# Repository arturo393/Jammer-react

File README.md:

# 🚨 Jammer-React

Sistema de complemento anti-jamming diseñado para dispositivos Teltonika FMA120, con arquitectura basada en FreeRTOS y comunicación Bluetooth.

## 📋 Descripción

El sistema Jammer-React es un dispositivo de seguridad vehicular que detecta y responde a intentos de jamming de señales GPS/GSM. Está diseñado para trabajar como complemento de los dispositivos Teltonika FMA120, proporcionando una capa adicional de protección contra interferencias maliciosas.

### 🎯 Características Principales

- **Detección automática de jamming** en tiempo real
- **Sistema de corta corriente** configurable 
- **Comunicación Bluetooth** para configuración remota
- **Sensor de puerta** integrado
- **Monitoreo de memoria** con comando de diagnóstico
- **LED indicador** de estados del sistema
- **Compatible con FreeRTOS**

## 🔧 Protocolo de Funcionamiento

### Algoritmo Principal

1. **Monitoreo Continuo**: Se revisa constantemente la entrada `JAMIN`
2. **Detección de Jamming**: Si `JAMIN == LOW`:
   - `JAMOUT = LOW` por 90 segundos
   - `DOUT` intercambia entre LOW y abierto durante 90 segundos
   - Se entra en **modo alarma** durante 90 segundos
3. **Activación por Puerta**: Si durante el modo alarma `DOORIN == Abierto`:
   - `JAMOUT = LOW` durante 5 minutos después que termine el modo alarma

### Estados del Sistema

- **Normal**: Monitoreo continuo sin detección de jamming
- **Alarma**: Jamming detectado, activación de contramedidas
- **Puerta Abierta**: Extensión del modo de protección

## 🏗️ Estructura del Proyecto

```
Jammer-react/
├── Hardware/              # Diseños de PCB y esquemáticos
│   ├── v1/               # Versión 1 del hardware
│   └── v2/               # Versión 2 del hardware
├── JammerRTOS/           # Código principal con FreeRTOS
├── jammerv2/             # Versión 2 del firmware
├── jammerv3/             # Versión 3 del firmware (sin FreeRTOS)
├── Simulation/           # Simulaciones SPICE
├── case/                 # Archivos para carcasa
├── logos/                # Recursos gráficos
├── CHANGELOG.md          # Historial de cambios
├── RELEASE_NOTES.md      # Notas de la versión actual
└── README.md            # Este archivo
```

## 🚀 Instalación y Configuración

### Prerrequisitos

- **PlatformIO** instalado
- **Arduino IDE** (opcional)
- Microcontrolador compatible con **ESP32/Arduino**
- Dispositivo **Teltonika FMA120**

### Configuración del Hardware

1. Conectar las entradas según el esquemático en `/Hardware/v2/`
2. Configurar los pines según la definición en el código
3. Verificar las conexiones de alimentación

### Compilación

```bash
# Usando PlatformIO
cd JammerRTOS
pio run

# Para upload
pio run --target upload
```

## 📊 Versiones

### Actual: v2.1 (Rama optimization)
- ✅ Función F() para mejora de estabilidad
- ✅ Comando `memtest` para diagnóstico
- ✅ Sistema de lectura de memoria mejorado
- 🔄 En pruebas: Optimizaciones del corta corriente

### Historial de Versiones

- **v2.1** (2018-12-18): Funciones Bluetooth y estado no volátil
- **v2.0** (2018-11-29): Reestructuración completa del código
- **v1.9.0** (2018-08-21): Correcciones críticas de estabilidad
- **v1.1** (2018-02-20): Variables de estado y sensores
- **v1.0** (2017-12-01): Versión inicial estable

Ver [CHANGELOG.md](CHANGELOG.md) para detalles completos.

## 🛠️ Configuración via Bluetooth

El sistema permite configuración remota via Bluetooth:

- **ID del dispositivo**: Configuración única por unidad
- **Estados del sistema**: Monitoreo en tiempo real
- **Parámetros de funcionamiento**: Ajuste de tiempos y umbrales
- **Comando memtest**: Diagnóstico de memoria

## 🔍 Diagnóstico y Debug

### Comando memtest
```
memtest
```
Proporciona información sobre:
- Uso actual de memoria
- Memoria disponible
- Estado de las tareas FreeRTOS

### LEDs Indicadores
- **LED Principal**: Estado general del sistema
- **Durante Alarma**: Parpadeo característico
- **Modo Configuración**: Patrón específico

## 📈 Especificaciones Técnicas

| Característica | Especificación |
|----------------|----------------|
| Microcontrolador | ESP32/Arduino compatible |
| Voltaje de operación | 12V DC |
| Consumo | <100mA en standby |
| Temperatura | -20°C a +60°C |
| Comunicación | Bluetooth 2.0/4.0 |
| Entradas digitales | 3 (JAMIN, DOORIN, GPS) |
| Salidas digitales | 2 (JAMOUT, DOUT) |

## 🤝 Contribución

1. Fork el proyecto
2. Crea una rama para tu feature (`git checkout -b feature/AmazingFeature`)
3. Commit tus cambios (`git commit -m 'Add some AmazingFeature'`)
4. Push a la rama (`git push origin feature/AmazingFeature`)
5. Abre un Pull Request

## 📝 Licencia

Este proyecto está bajo la licencia especificada en el archivo [LICENSE](LICENSE).

## 👨‍💻 Autor

**Arturo Veras** - [@arturo393](https://github.com/arturo393)

## 📞 Soporte

Para soporte técnico o preguntas:
- Abre un [issue](https://github.com/arturo393/Jammer-react/issues)
- Consulta la documentación en [RELEASE_NOTES.md](RELEASE_NOTES.md)

---

⚠️ **Nota**: Este sistema está diseñado para uso legítimo de seguridad vehicular. Asegúrate de cumplir con las regulaciones locales sobre dispositivos de radiofrecuencia.

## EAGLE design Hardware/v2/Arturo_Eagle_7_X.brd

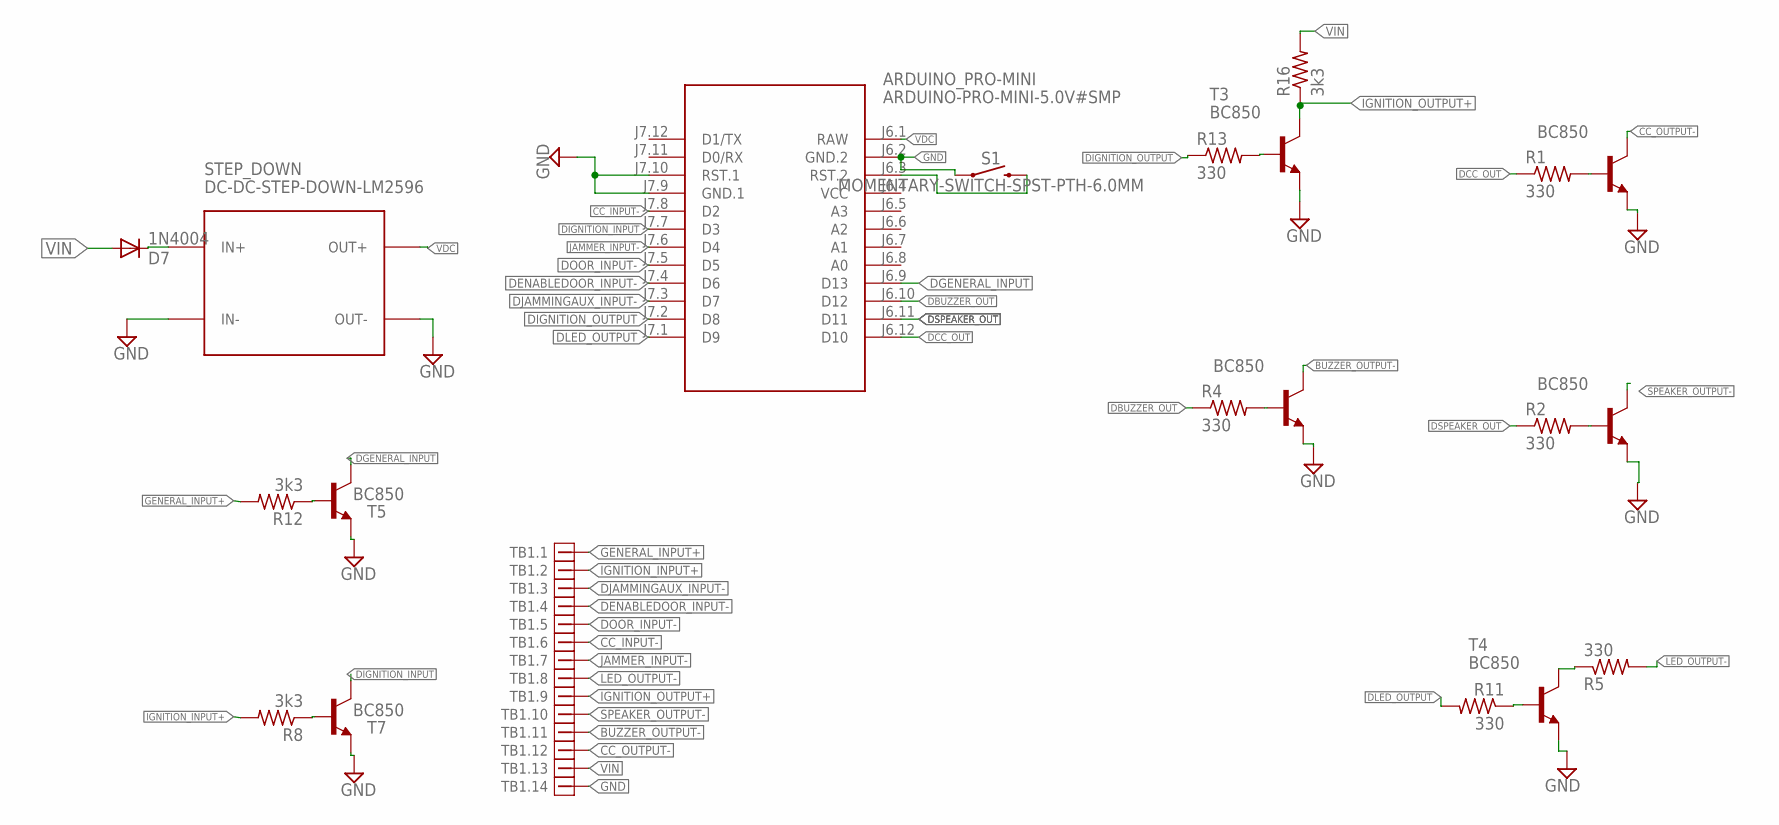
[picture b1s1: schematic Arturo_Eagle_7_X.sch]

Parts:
ARDUINO_PRO-MINI: ARDUINO-PRO-MINI-5.0V#SMP; ARDUINO-PRO-MINI#SMP
D7: 1N4004; DO41-10
R1, R2, R4, R5, R11, R13: 330; R0805
R8, R12, R16: 3k3; R0805
S1: MOMENTARY-SWITCH-SPST-PTH-6.0MM; TACTILE_SWITCH_PTH_6.0MM
STEP_DOWN: DC-DC-STEP-DOWN-LM2596
T1, T3, T4, T5, T6, T7, T8: BC850; SOT23
TB1: TB_PHOENIX; TERMINAL_BLOCK_14POS

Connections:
BUZZER_OUTPUT-: T6.3 (C), TB1.11, TB1.25
CC_INPUT-: ARDUINO_PRO-MINI.J7.8 (D2), TB1.6, TB1.20
CC_OUTPUT-: T8.3 (C), TB1.12, TB1.26
DBUZZER_OUT: ARDUINO_PRO-MINI.J6.10 (D12), R4.1
DCC_OUT: ARDUINO_PRO-MINI.J6.12 (D10), R1.1
DENABLEDOOR_INPUT-: ARDUINO_PRO-MINI.J7.4 (D6), TB1.4, TB1.18
DGENERAL_INPUT: ARDUINO_PRO-MINI.J6.9 (D13), T5.3 (C)
DIGNITION_INPUT: ARDUINO_PRO-MINI.J7.7 (D3), T7.3 (C)
DIGNITION_OUTPUT: ARDUINO_PRO-MINI.J7.2 (D8), R13.1
DJAMMINGAUX_INPUT-: ARDUINO_PRO-MINI.J7.3 (D7), TB1.3, TB1.17
DLED_OUTPUT: ARDUINO_PRO-MINI.J7.1 (D9), R11.2
DOOR_INPUT-: ARDUINO_PRO-MINI.J7.5 (D5), TB1.5, TB1.19
DSPEAKER_OUT: ARDUINO_PRO-MINI.J6.11 (D11), R2.1
GENERAL_INPUT+: R12.2, TB1.1, TB1.15
GND: ARDUINO_PRO-MINI.J6.2 (GND.2), ARDUINO_PRO-MINI.J7.9 (GND.1), ARDUINO_PRO-MINI.J7.10 (RST.1), S1.1, STEP_DOWN.IN-, STEP_DOWN.OUT-, T1.2 (E), T3.2 (E), T4.2 (E), T5.2 (E), T6.2 (E), T7.2 (E), T8.2 (E), TB1.14, TB1.28
IGNITION_INPUT+: R8.2, TB1.2, TB1.16
IGNITION_OUTPUT+: R16.1, T3.3 (C), TB1.9, TB1.23
JAMMER_INPUT-: ARDUINO_PRO-MINI.J7.6 (D4), TB1.7, TB1.21
LED_OUTPUT-: R5.2, TB1.8, TB1.22
unnamed: R12.1, T5.1 (B)
unnamed: R13.2, T3.1 (B)
unnamed: R1.2, T8.1 (B)
unnamed: R2.2, T1.1 (B)
unnamed: R4.2, T6.1 (B)
unnamed: R5.1, T4.3 (C)
unnamed: ARDUINO_PRO-MINI.J6.3 (RST.2), S1.3 (2)
unnamed: R11.1, T4.1 (B)
unnamed: R8.1, T7.1 (B)
unnamed: D7.C, STEP_DOWN.IN+
SPEAKER_OUTPUT-: T1.3 (C), TB1.10, TB1.24
VCC: ARDUINO_PRO-MINI.J6.4 (VCC)
VDC: ARDUINO_PRO-MINI.J6.1 (RAW), STEP_DOWN.OUT+
VIN: D7.A, R16.2, TB1.13, TB1.27

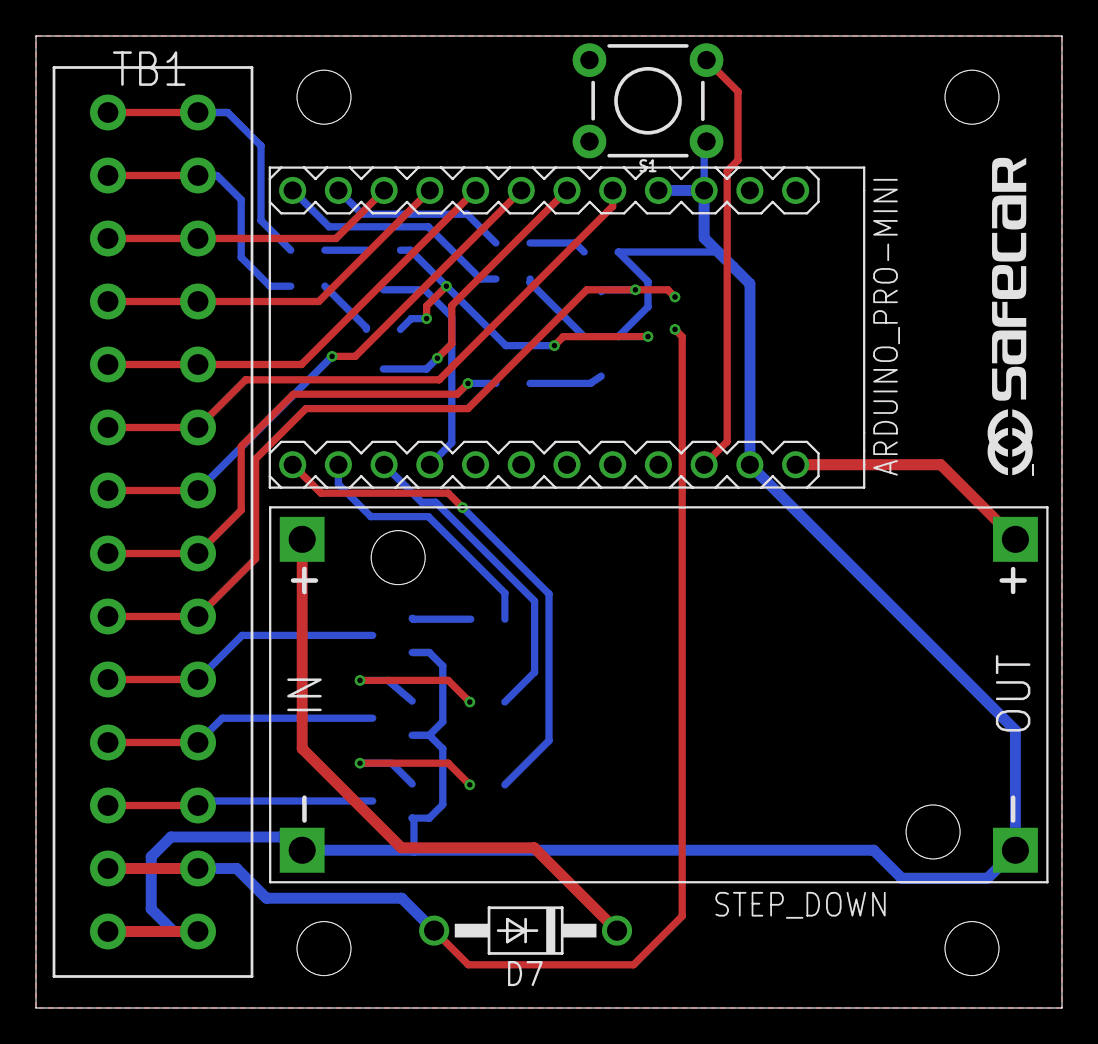
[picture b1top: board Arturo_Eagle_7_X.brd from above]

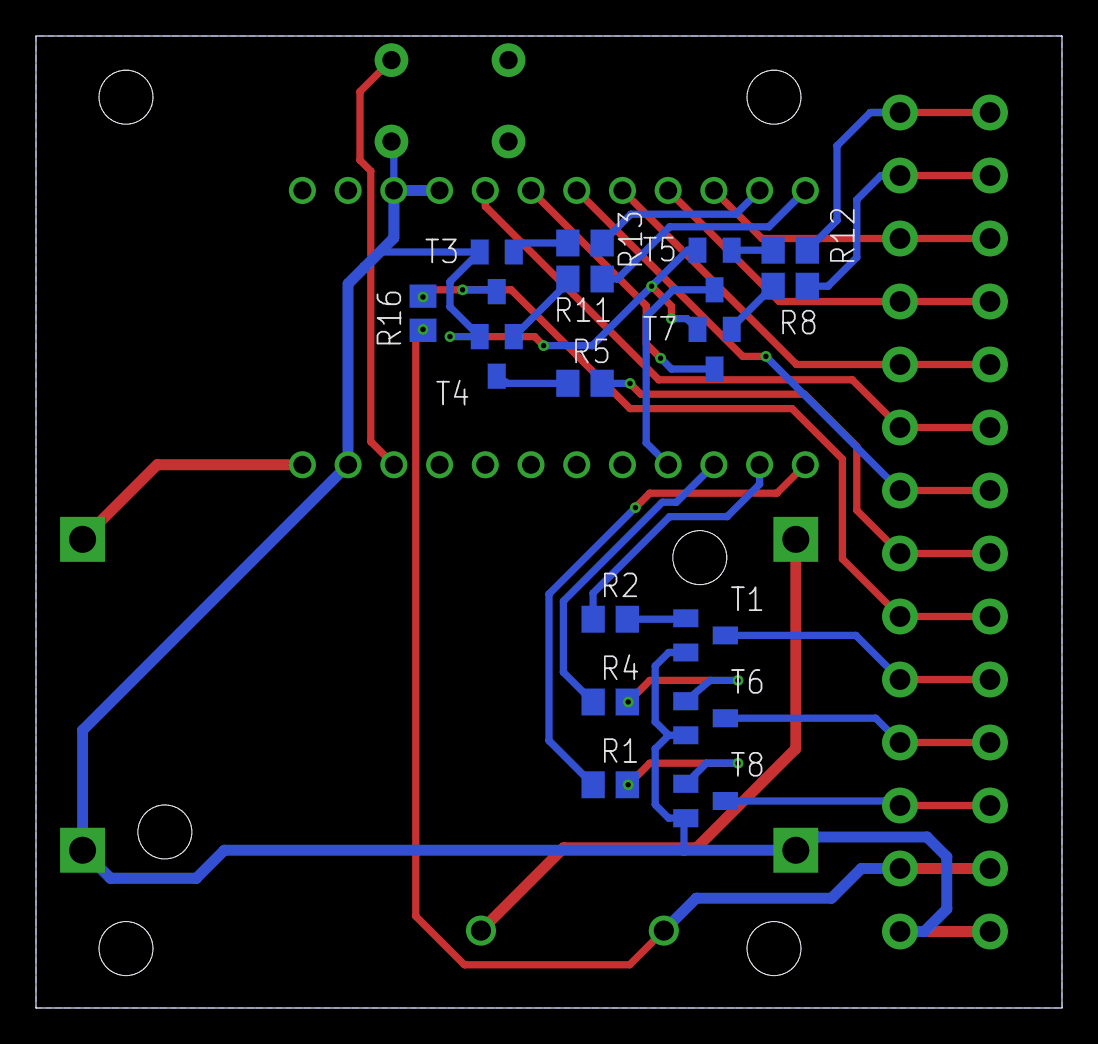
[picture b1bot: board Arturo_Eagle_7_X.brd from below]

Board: 2 copper layers, 57.0 x 54.0 mm, 21 parts (16 on the bottom side), 32 nets.

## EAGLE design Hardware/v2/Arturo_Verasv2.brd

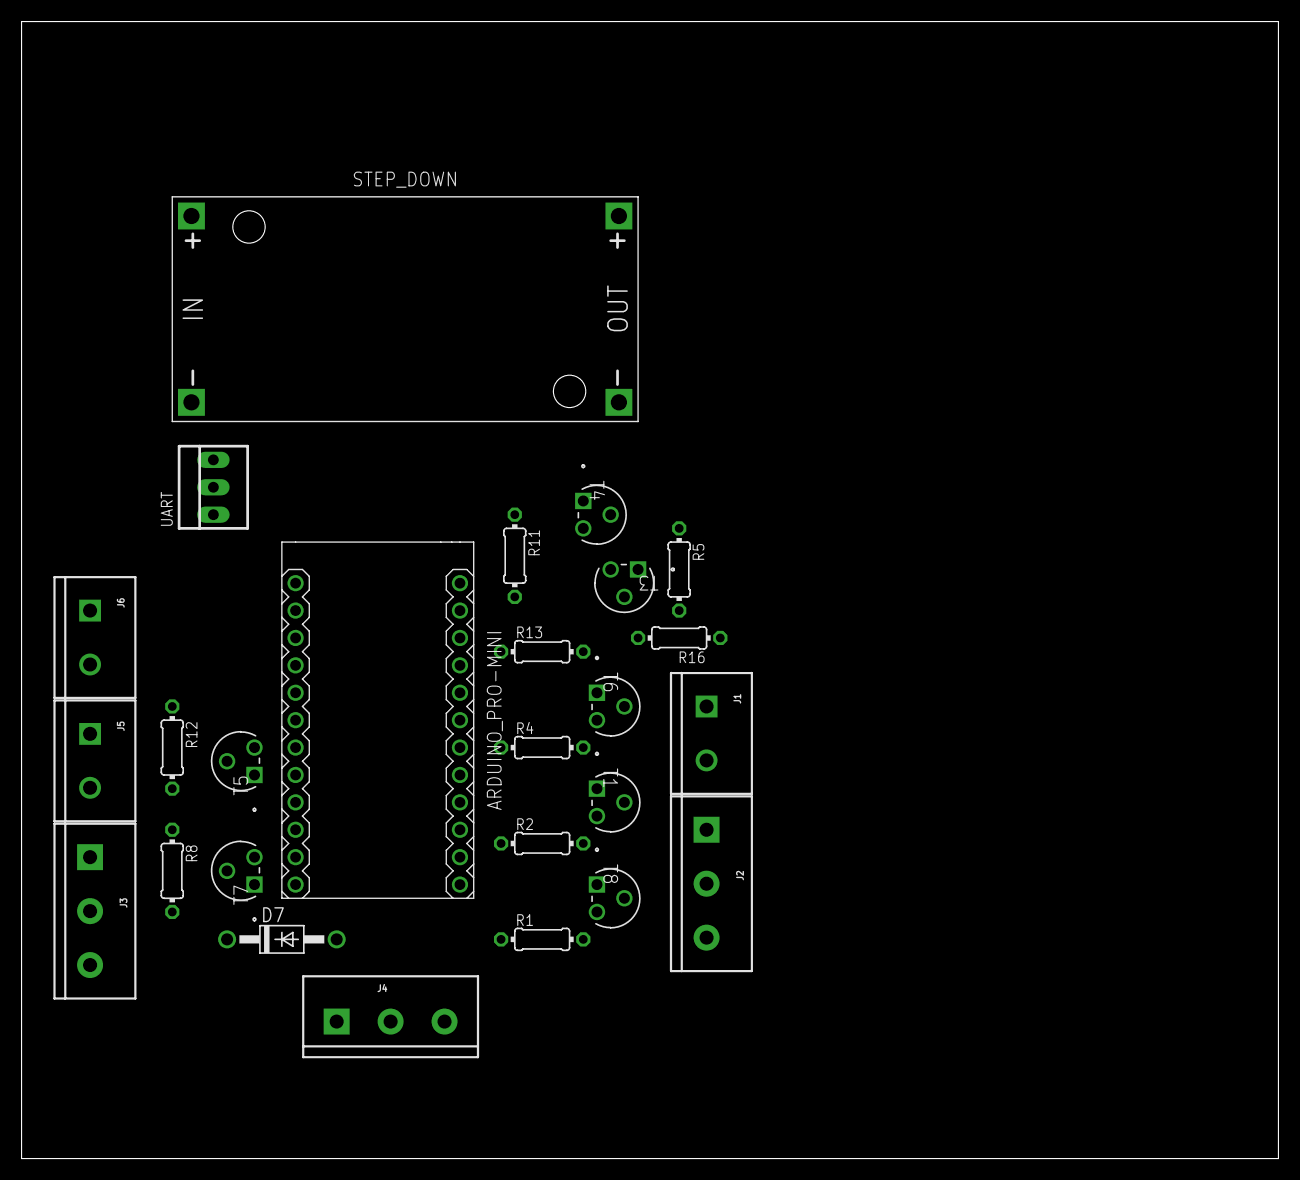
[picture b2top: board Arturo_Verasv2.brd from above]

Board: 2 copper layers, 116.5 x 105.4 mm, 26 parts (0 on the bottom side), 34 nets, no tracks yet.

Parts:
ARDUINO_PRO-MINI: ARDUINO-PRO-MINI-5.0V#SMP; ARDUINO-PRO-MINI#SMP
D7: 1N4004; DO41-10
J1, J5, J6: SCREWTERMINAL-5MM-2
J2, J3, J4: SCREWTERMINAL-5MM-3
R1, R2, R4, R5, R13: 330; 0204/7
R8, R12, R16: 3k3; 0204/7
R11: 47k; 0204/7
STEP_DOWN: DC-DC-STEP-DOWN-LM2596
T1, T3, T4, T5, T6, T7, T8: MPSA06; TO-92_2
UART: 22-23-2031

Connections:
BUZZER_OUTPUT-: J1.2, T6.3
CC_OUTPUT-: J2.2, T8.3
DBUZZER_OUT: ARDUINO_PRO-MINI.J6.10, R4.1
DCC_OUT: ARDUINO_PRO-MINI.J6.12, R1.1
DDOOR_INPUT-: ARDUINO_PRO-MINI.J7.1, J3.3
DENABLEDOOR_INPUT-: ARDUINO_PRO-MINI.J7.4, J3.1
DGENERAL_INPUT: ARDUINO_PRO-MINI.J7.5, T5.3
DIGNITION_INPUT: ARDUINO_PRO-MINI.J7.2, T7.3
DJAMMINGAUX_INPUT-: ARDUINO_PRO-MINI.J7.7, J6.2
DLED_OUTPUT: ARDUINO_PRO-MINI.J7.3, R11.2
DSPEAKER_OUT: ARDUINO_PRO-MINI.J6.11, R2.1
DTDIN2_OUT-: ARDUINO_PRO-MINI.J6.9, R13.1
DTDOUT1_INPUT-: ARDUINO_PRO-MINI.J7.6, J5.1
DTDOUT2_INPUT-: ARDUINO_PRO-MINI.J7.8, J6.1
GENERAL_INPUT+: J5.2, R12.2
GND: ARDUINO_PRO-MINI.J6.2, J4.2, R16.1, STEP_DOWN.IN-, STEP_DOWN.OUT-, T1.1, T4.1, T5.1, T6.1, T7.1, T8.1
IGNITION_INPUT+: J3.2, R8.2
LED_OUTPUT-: J2.3, R5.2
unnamed: R12.1, T5.2
unnamed: R13.2, T3.2
unnamed: R1.2, T8.2
unnamed: R2.2, T1.2
unnamed: R4.2, T6.2
unnamed: R5.1, T4.3
unnamed: ARDUINO_PRO-MINI.J7.12, UART.3
unnamed: ARDUINO_PRO-MINI.J7.11, UART.2
unnamed: ARDUINO_PRO-MINI.J7.9, UART.1
unnamed: R11.1, T4.2
unnamed: R8.1, T7.2
unnamed: D7.C, STEP_DOWN.IN+
SPEAKER_OUTPUT-: J2.1, T1.3
TDIN2_OUTPUT+: J1.1, R16.2, T3.1
VIN: D7.A, J4.1, T3.3
VOUT: ARDUINO_PRO-MINI.J6.1, J4.3, STEP_DOWN.OUT+

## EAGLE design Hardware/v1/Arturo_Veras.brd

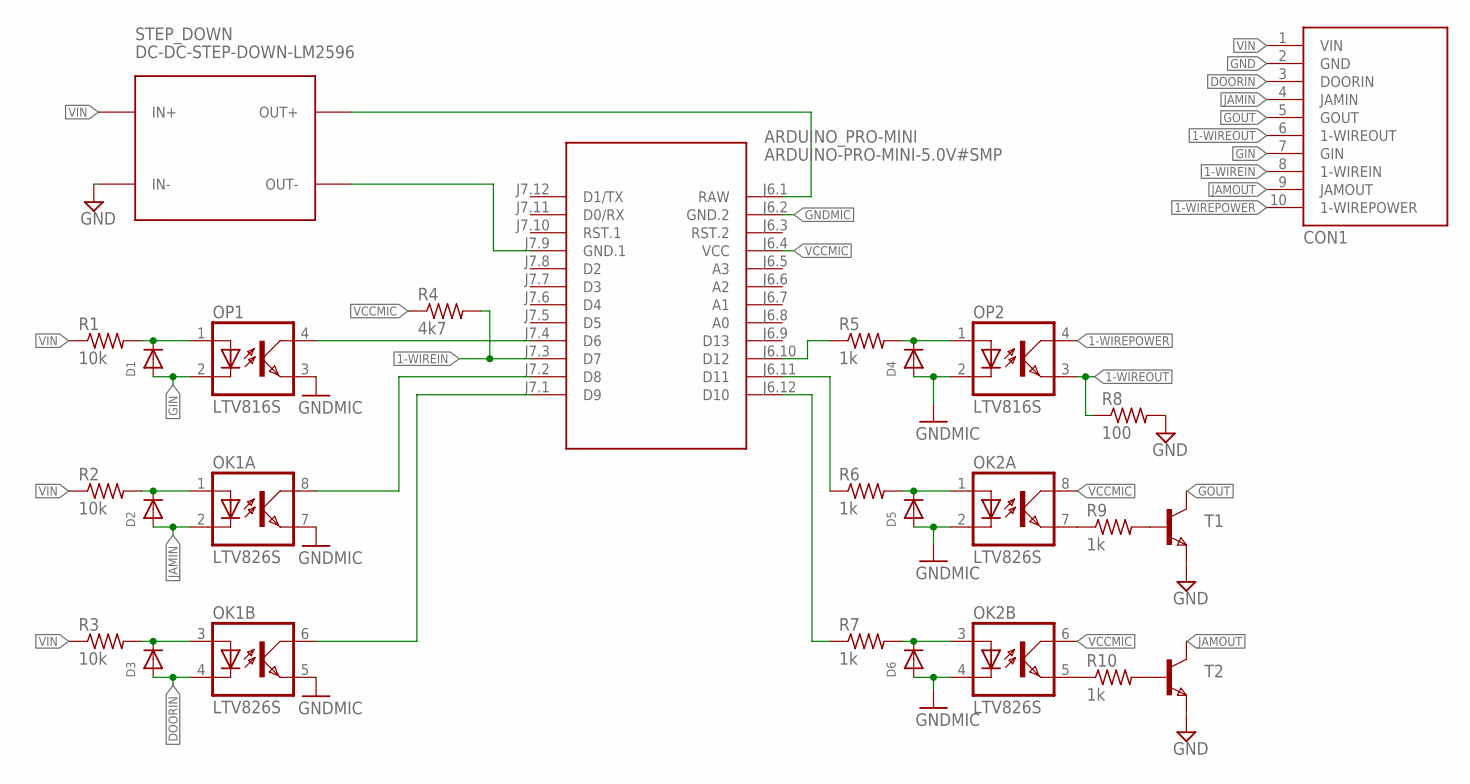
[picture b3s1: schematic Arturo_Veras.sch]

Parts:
ARDUINO_PRO-MINI: ARDUINO-PRO-MINI-5.0V#SMP; ARDUINO-PRO-MINI#SMP
CON1: TIN_HEADER_10POS; MICRO_MATE_N_LOK_TRUEHOLE_10POS
D1, D2, D3, D4, D5, D6: DIODESOD-323F; SOD-323F
OK1, OK2: LTV826S; DIL8-SMD
OP1, OP2: LTV816S; SMD4
R1, R2, R3: 10k; R0603
R4: 4k7; R0603
R5, R6, R7, R9, R10: 1k; R0603
R8: 100; R0603
STEP_DOWN: DC-DC-STEP-DOWN-LM2596
T1, T2: PBSS4360Z; SOT223

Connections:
1-WIREIN: ARDUINO_PRO-MINI.J7.3 (D7), CON1.8 (1-WIREIN), R4.2
1-WIREOUT: CON1.6 (1-WIREOUT), OP2.3 (EMIT), R8.1
1-WIREPOWER: CON1.10 (1-WIREPOWER), OP2.4 (COL)
DOORIN: CON1.3 (DOORIN), D3.A, OK1.4 (C)
GIN: CON1.7 (GIN), D1.A, OP1.2 (C)
GND: CON1.2 (GND), R8.2, STEP_DOWN.IN-, T1.3 (E), T2.3 (E)
GNDMIC: ARDUINO_PRO-MINI.J6.2 (GND.2), D4.A, D5.A, D6.A, OK1.5 (EMIT), OK1.7 (EMIT), OK2.2 (C), OK2.4 (C), OP1.3 (EMIT), OP2.2 (C)
GOUT: CON1.5 (GOUT), T1.2 (C), T1.4 (C)
JAMIN: CON1.4 (JAMIN), D2.A, OK1.2 (C)
JAMOUT: CON1.9 (JAMOUT), T2.2 (C), T2.4 (C)
unnamed: ARDUINO_PRO-MINI.J7.9 (GND.1), STEP_DOWN.OUT-
unnamed: ARDUINO_PRO-MINI.J6.1 (RAW), STEP_DOWN.OUT+
unnamed: ARDUINO_PRO-MINI.J7.4 (D6), OP1.4 (COL)
unnamed: D1.C, OP1.1 (A), R1.2
unnamed: ARDUINO_PRO-MINI.J6.10 (D12), R5.1
unnamed: D2.C, OK1.1 (A), R2.2
unnamed: ARDUINO_PRO-MINI.J7.2 (D8), OK1.8 (COL)
unnamed: D3.C, OK1.3 (A), R3.2
unnamed: D4.C, OP2.1 (A), R5.2
unnamed: ARDUINO_PRO-MINI.J7.1 (D9), OK1.6 (COL)
unnamed: OK2.7 (EMIT), R9.1
unnamed: ARDUINO_PRO-MINI.J6.11 (D11), R6.1
unnamed: D5.C, OK2.1 (A), R6.2
unnamed: ARDUINO_PRO-MINI.J6.12 (D10), R7.1
unnamed: D6.C, OK2.3 (A), R7.2
unnamed: OK2.5 (EMIT), R10.1
unnamed: R9.2, T1.1 (B)
unnamed: R10.2, T2.1 (B)
VCCMIC: ARDUINO_PRO-MINI.J6.4 (VCC), OK2.6 (COL), OK2.8 (COL), R4.1
VIN: CON1.1 (VIN), R1.1, R2.1, R3.1, STEP_DOWN.IN+

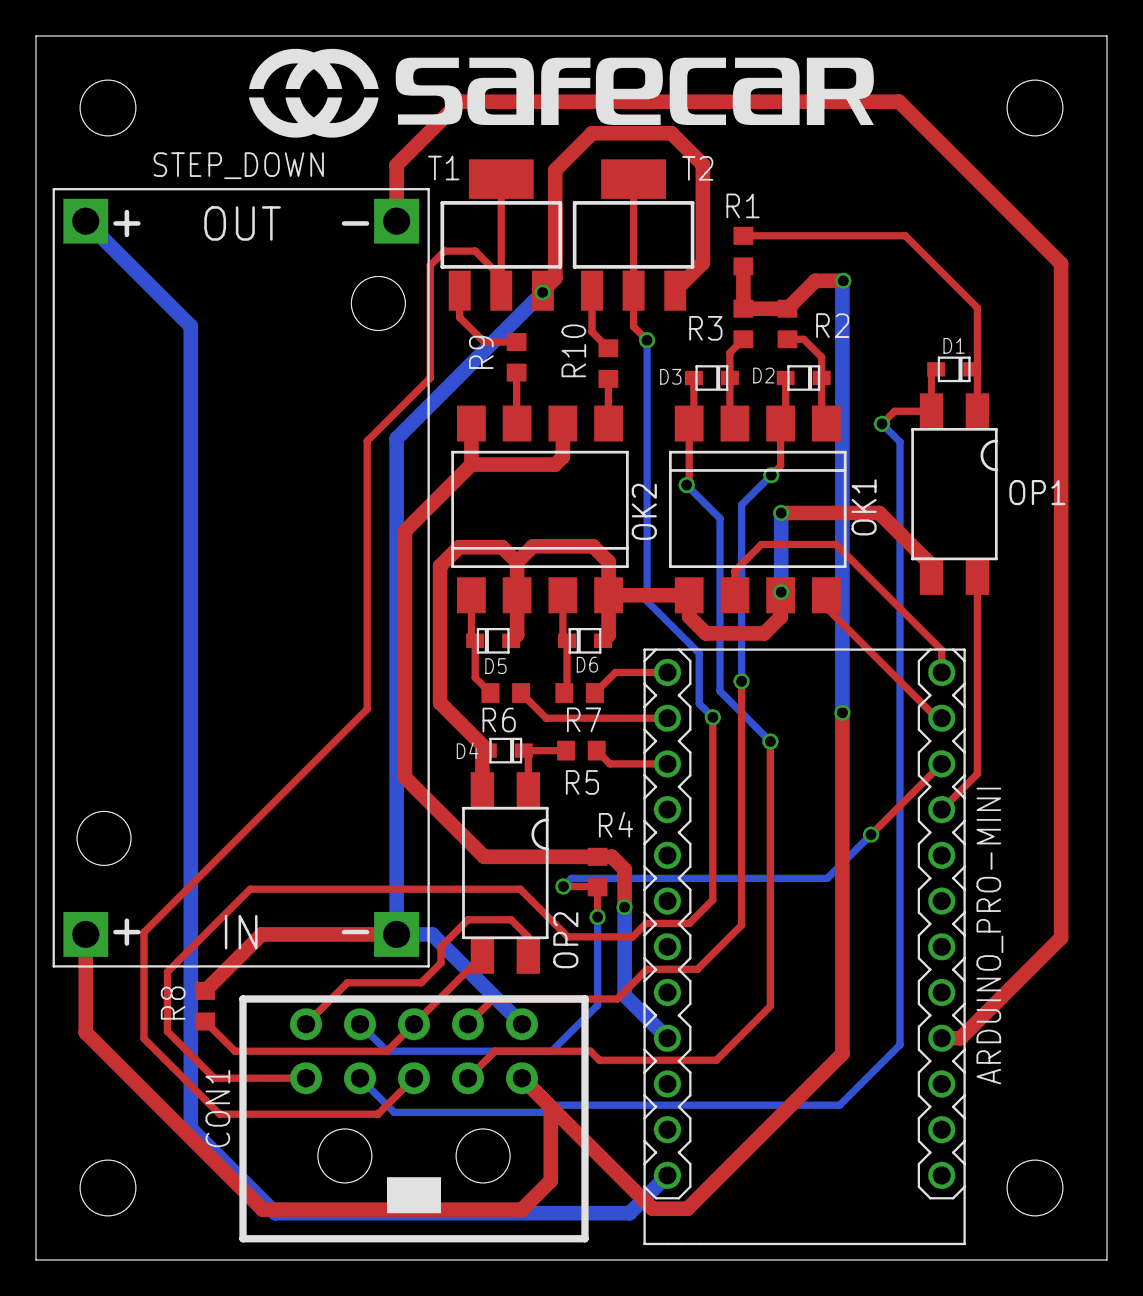
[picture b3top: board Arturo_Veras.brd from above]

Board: 2 copper layers, 59.5 x 68.0 mm, 25 parts (0 on the bottom side), 30 nets.

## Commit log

2017-08-24 cambio en el hardware y el código del jammer
2017-08-25 update led settings
2017-08-29 update library
2017-08-29 new
    copy of jammer1 for freertos implementation
2017-08-29 config
    configuration compiler update
2017-08-29 git
    git config
2017-08-29 jammer
    jammer function ready
2017-09-04 Escritura ibutton
    Se modifica los pines para poder escribir en otro dispositivo de 3.3 v , falta probar
2017-09-12 new design
2017-10-26 agregué ibutton y jammer en freertos
2017-11-01 actualizacion general
2017-11-01 primer makefile
2017-11-23 elimina safecar.brd porque el archivo esta malo. Se agrega un nuevo código de lectura del ibuton
2017-11-23 modificaciones de pines para la placa. jammev3 es una versión sin freertos
2017-11-23 No se que hice
    Este codigo funcionó para la comunicación serial
2017-11-28 Simulacion de las entradas y salidas en formato spice
2017-11-28 logos de safecar
2017-11-28 archivos inncesesarios
2017-12-01 se arreglan los pines para la placa. Se agrega Serial.print para la puerta. Se corrige las salidas para el corta corriente. Se prueba con el LEDPIN pero aún no funciona
2017-12-01 Agregó LEDPIN durante el JAMAlert.
2017-12-01 Actualizo la distribución de pines. Se agregan los archivos GERBER
2017-12-01 Add a to do list for improve the v.1 version
2017-12-01 Number view fixed
2017-12-28 Todo list and software description
    Se borra la lista por hacer.
    Se agrega la descirpcion del algorimo.
2018-01-02 se borran librerias inncesarias
2018-01-29 se agrega la notificación cada 10 minutos del dispositivo
2018-01-29 blabla
2018-01-29 arreglo del merge}
2018-02-05 Elinino archivos y codigos innecesarios.
2018-02-20 Remove unncessary library
2018-02-20 Added cut-engine connection without relay
2018-02-20 delay for pin output stabilizer
2018-02-20 remove change of state on keep alive signal. Always on
2018-02-20 added state variables to cut-engine relay or not and the door sensor.
2018-06-05 comienzo de versión 2
    Se agrega nuevos componentes a la placa y se se hace un código con FreeRtos.
2018-06-06 Hardware update
    se ordena el ciruito para que quede más simple revisar las señales.
2018-06-06 hardware update
    se agregan más componentes
2018-06-13 Esquematico
    se hace más simple el esquemático
2018-06-21 Se agrega pin
    nuevos pines agregados
2018-06-26 Mejora del Encendido de Motor
    Se mejora la salida del encendido de motor porque.
    Se invierte la salida jammeralert y se quita de la tarea Jammer
2018-06-26 no se que hice
2018-06-26 nueva
2018-07-13 se agrega el activar el motor cuando se corta por jammer
2018-07-17 Circuito de pruebas
    pruebas de corrientes para transistores
2018-07-17 Cambios en las piezas
    se cambian los transistores, las resistencias y los conectores.
2018-07-17 Más cambios
    más cambios en conectores, transistores y resistencias
2018-07-18 Comentarios
2018-08-08 Se cambia el nombre del pin
2018-08-08 Se cambia engine por ignition
2018-08-14 diseño de tomas
    esta es la versión corregida que entregó tomas y es la que enviamos a fabricar
2018-08-14 Taskcreate priority
    Se arregla el error de de asignar prioridades mayores a 4 a la creación de las tareas. Además elimina la tarea Door y se junta todo en Ignitionnotificationtask
2018-08-17 taskinterrupt
    se mejora la detección de interrupciones. queda pendiente la activación de la interrupcion por la notifiación de evento.
2018-08-18 Falta arreglar la interrupción que se ejecuta cuando se activa la notificación
2018-08-21 cambie el vPrintStringAndNumber por Serial.print porque da errores.
2018-08-21 Se eliminan algunos print que hacen malfuncionar el programa
2018-08-22 Se arregla el error que genrea las interrupciones!!
2018-09-20 se agrega un tiempo definido en TIME_AFTER_OPEN_DOOR para encender el CC
2018-09-20 Se agrega pin para que funcione con positivo
2018-10-16 se agrega para debug
2018-10-29 se mejora el serial.print
2018-10-29 agrego posibilidad de cambiar para ambos sensores según DOORSENSOR
2018-10-31 se hacen mejoras al protocolo puerta seguras
2018-11-19 Se lee y se escriben los caracteres, falta leer y comprar un string.
2018-11-22 se cambia la estructura del código, está malo aún
2018-11-29 Se cambia la estructura completamente. versión funcional, falta probar.
2018-12-13 se agrega el id por bluetooth. Falta que hacer para reiniciar con el baudrate normal.
2018-12-18 Se agrega función de bloquear con bluetooth. Falta probar
2018-12-20 se agrega variable no volatil al estado del jammer.
2019-05-08 se agrega el estado y la versión
2019-05-29 new arquitecture
2019-05-29 eliminé warnings
2019-05-31 todas las tareas funncionan por separado, falta reajustar el heap Size
2019-05-31 buscando el stack perfecto
2019-06-04 reduzco el configMINIMAL_STACK_SIZE, hago mejoras en el código
2019-06-20 Se elimina el cambio del corta corriente por la entrada CCDisable
2019-07-03 mejoras al apagado automático
2019-07-08 mejoras en el desbloqueo por gps
2019-07-12 Se agregan filtros a las entradas
2019-07-24 Se maneja la excepción del buffer para el seria1 read
2019-07-26 cambios en el bluetooth
2019-08-07 se agregan estados y se mejora la config por bluetooth
2019-08-16 cambios menores
2019-08-19 se agrega nuevo estado para acceder más rápido a la app.
2019-09-16 se agrega la puerta
2019-11-20 se agrega testtask
    tarea para probar las entradas y salidas del AJ
2019-11-21 output pin
    se agregan los pin de salida
2019-11-21 new algorithm
2019-11-25 compila pero falla cuando se agregan todas las tareas
2019-11-26 se termina la primera version del testtask
2019-11-27 se prueba nueva versión del testtask
2020-02-05 codigo más limpio y mejoras en la tareas Test
2020-03-06 version de pruebas sin la tarea Test
2020-03-09 agrego comando memtest para revisar memoria y se mejoran algunos print
2020-03-13 mejoras para evitar que se quede pegado
2020-03-13 quité el timer de la memoria, más estable
2020-03-18 aún se queda pegado el corta corriente.
2020-03-18 se agrega el codigo para leer memoria
2020-03-19 siguen en pruebas, falla el corta corriente
2020-03-25 se agrega la funciona F() y mejora la establidad, aún en pruebas
2025-08-27 docs: Add comprehensive documentation
    - Add detailed CHANGELOG.md with version history from commits
    - Add RELEASE_NOTES.md for optimization branch
    - Completely rewrite README.md with professional structure
    - Include installation instructions, specifications, and usage guide
    - Add project structure, troubleshooting, and contribution guidelines
2025-08-27 merge: Integrate documentation from optimization branch
    - Add comprehensive CHANGELOG.md with complete version history
    - Add detailed RELEASE_NOTES.md for current state
    - Update README.md with professional structure and documentation
    - Preserve master branch stability while adding documentation improvements

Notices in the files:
parts and their libraries:
diy-modules: Released under the Creative Commons Attribution 4.0 International License: http://creativecommons.org/licenses/by/4.0
SparkFun-Switches: Licensing: Creative Commons ShareAlike 4.0 International - https://creativecommons.org/licenses/by-sa/4.0
